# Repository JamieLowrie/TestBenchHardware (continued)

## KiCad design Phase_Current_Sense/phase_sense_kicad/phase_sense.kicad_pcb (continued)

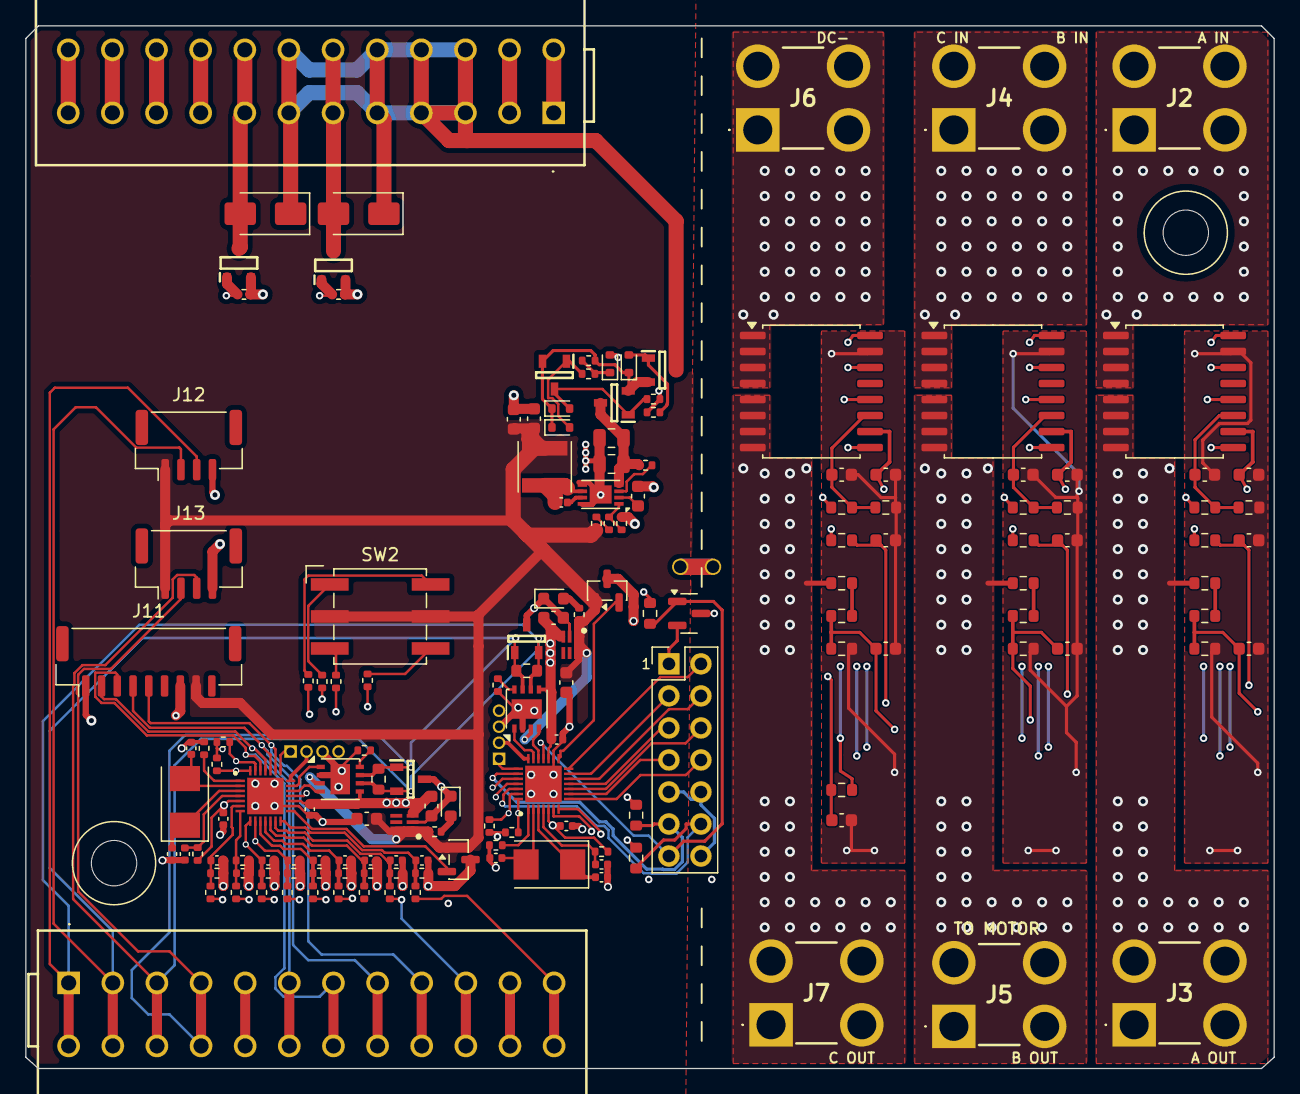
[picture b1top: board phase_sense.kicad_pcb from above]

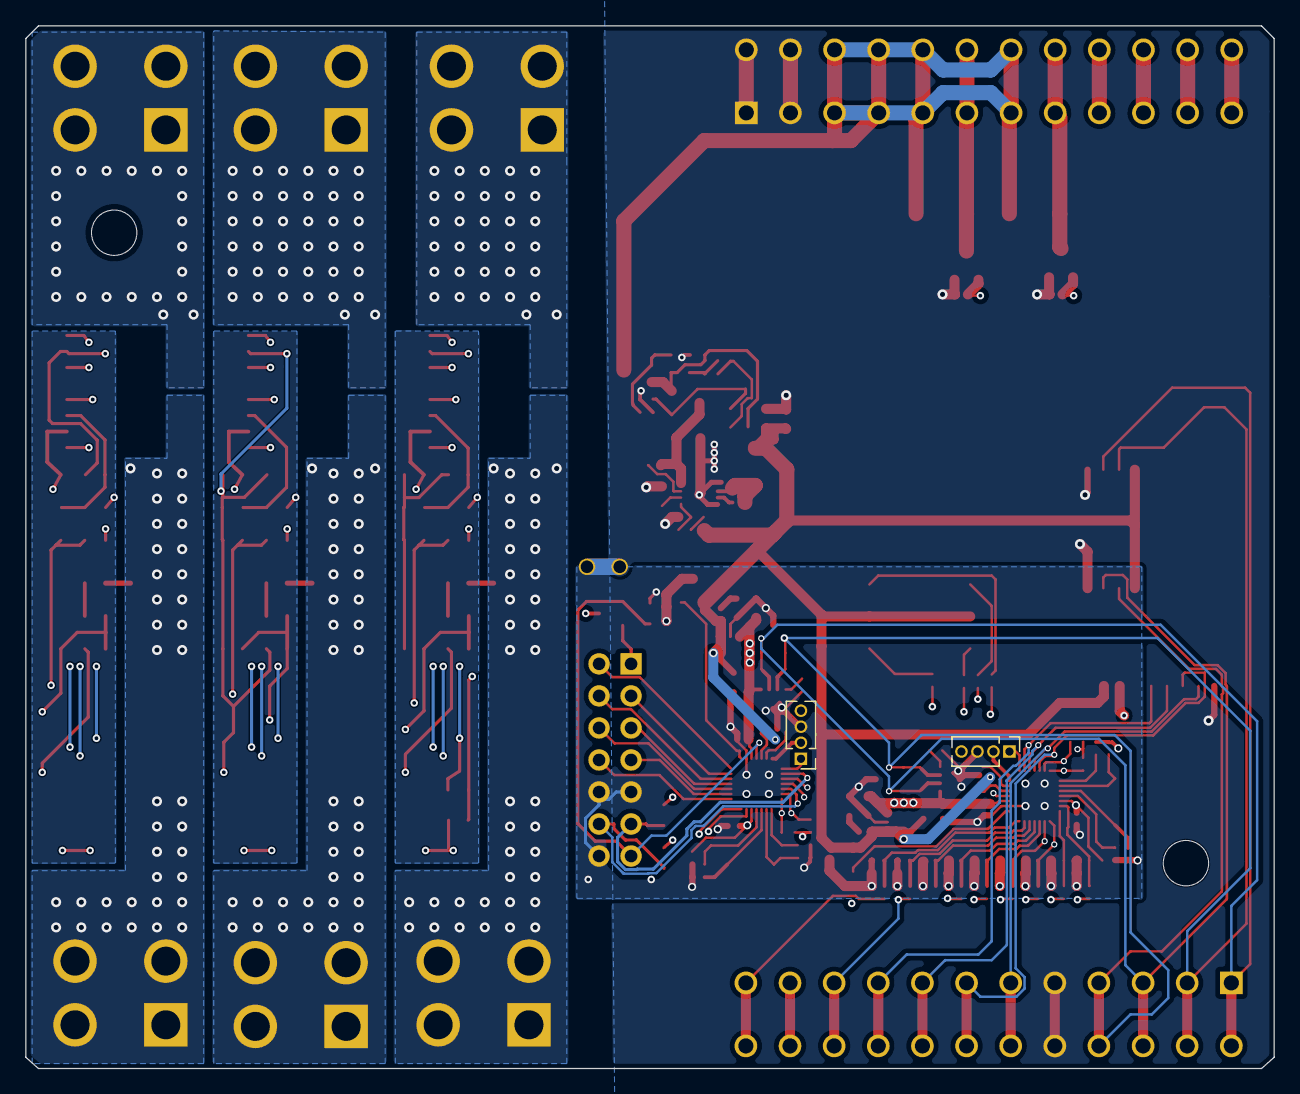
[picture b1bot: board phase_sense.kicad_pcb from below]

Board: 4 copper layers, 99.0 x 82.7 mm, 159 parts (2 on the bottom side), 101 nets.

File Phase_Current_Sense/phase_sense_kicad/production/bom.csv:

Designator,Footprint,Quantity,Value,LCSC Part #
C1,0603,1,10u,C19702
"C10, C18, C4, C6, C7",0603,5,22uF,C59461
"C11, C12, C21, C22, C31, C32",0603,6,100n,C14663
"C13, C23, C33",0603,3,10n,C57112
"C14, C24, C34",0603,3,22n,C21122
"C15, C19, C29, C35, C40, C42, C5",0402,7,0.1uF,C1525
"C16, C17, C8, C9",0402,4,20pF,C1554
"C2, C3",0805,2,10uF,C15850
"C20, C25, C26, C27, C38, C39",0402,6,1nF,C1523
"C28, C36, C37",0402,3,10nF,C15195
"C30, C41",0603,2,4.7uF, C19666
"D1, D3, D4",D_SOD-523,3,Zener 15V,C550633
"D11, D12",D_SMA,2,SS310,C15874
D2,D_SOD-523,1,Zener 25V,C559071
"D5, D6",0603,2,LED,C2286
"H1, H2",CDIB_Pillar_No6_Screw,2,No6,
"IC1, IC3",SON50P150X150X80-6N,2,TLV70033DSER,C97256
"IC2, IC4",QFN40P400X400X80-29N-D,2,CH32V203G6U6,C5142280
"IC6, IC7",SOTFL95P240X110-3N,2,ZXMS6004FFQ-7,C95063
J1,PinHeader_2x07_P2.54mm_Vertical,1,TO_MCU,
"J10, J9",PinHeader_1x04_P1.27mm_Vertical,2,1.27Debug,C161692
J11,JST_GH_BM09B-GHS-TBT_1x09-1MP_P1.25mm_Vertical,1,Conn_01x08_Pin,DNF
"J12, J13",JST_GH_BM04B-GHS-TBT_1x04-1MP_P1.25mm_Vertical,2,CAN,DNF
"J2, J3, J4, J5, J6, J7",AMT0440007DB0000G,6,AMT0440007DB0000G,C481447
"J20, J25",26011112,2,2601-1112,
L1,L_Vishay_IFSC-1515AH_4x4x1.8mm,1,22uH,C5363803
Q1,SOT-23,1,AO3401A,C15127
"Q2, Q4",SOT95P230X110-3N,2,60V2APMOS,C5148659
Q3,SOT95P230X110-3N,1,60VPMOS,C5148659
"R1, R12, R2, R22, R3, R32, R4",0603,7,10k,C25804
"R10, R40, R41, R42, R43, R5, R53, R6, R60, R63, R64, R65, R66, R7, R8, R9",0402,16,10K,C25744
"R102, R103",0402,2,22K,C25768
"R11, R21, R31",0603,3,33k,C4216
"R13, R23, R33",0603,3,1k,C21190
"R14, R15, R24, R25, R34, R35",0603,6,47k,C25819
"R16, R26, R36",0603,3,2.7k,C13167
R17,0402,1,51K,C25794
R18,0402,1,3.9K,C51721
"R19, R20, R27, R28, R29, R30, R37, R38, R39",0402,9,470K,C25790
"R44, R45, R46, R47, R48, R49, R50, R56, R57",0402,9,510K,C11616
"R51, R58",0402,2,1K,C11702
"R52, R59",0603,2,DNF,DNF
"R54, R55, R61, R62",0402,4,2K,C4109
SW2,Nidec_Copal_SH-7010B,1,SW_Coded_SH-7050,C5183894
"U1, U2, U3",SOIC-16W_7.5x10.3mm_P1.27mm,3,ACS37002LMABTR-066B3,C3684355
U4,DFN-8-1EP_3x2mm_P0.5mm_EP1.75x1.45mm,1,MCP16311MNY,C510882
"U5, U7",DFN-8-1EP_3x3mm_P0.65mm_EP1.55x2.4mm,2,TJA1044GTK/3Z,C2157795
"U6, U8",SOT-23,2,REF3025,C11334
"Y1, Y2",Crystal_SMD_5032-2Pin_5.0x3.2mm,2,8Mhz, C115962
"Z1, Z2",SOT95P230X110-3N,2,"PESD1CAN,215",C15771

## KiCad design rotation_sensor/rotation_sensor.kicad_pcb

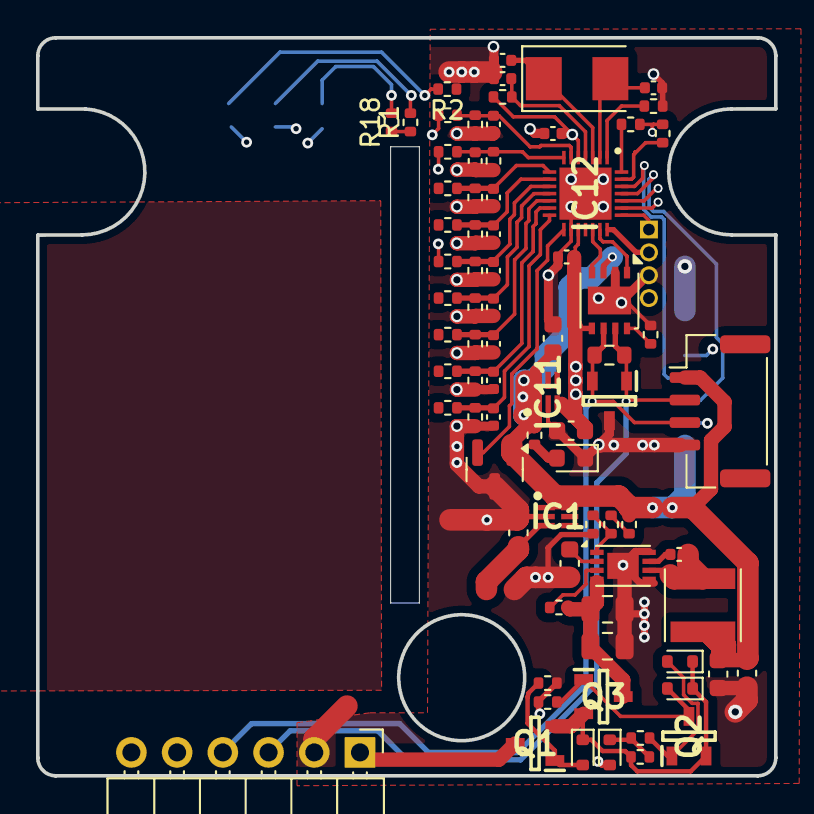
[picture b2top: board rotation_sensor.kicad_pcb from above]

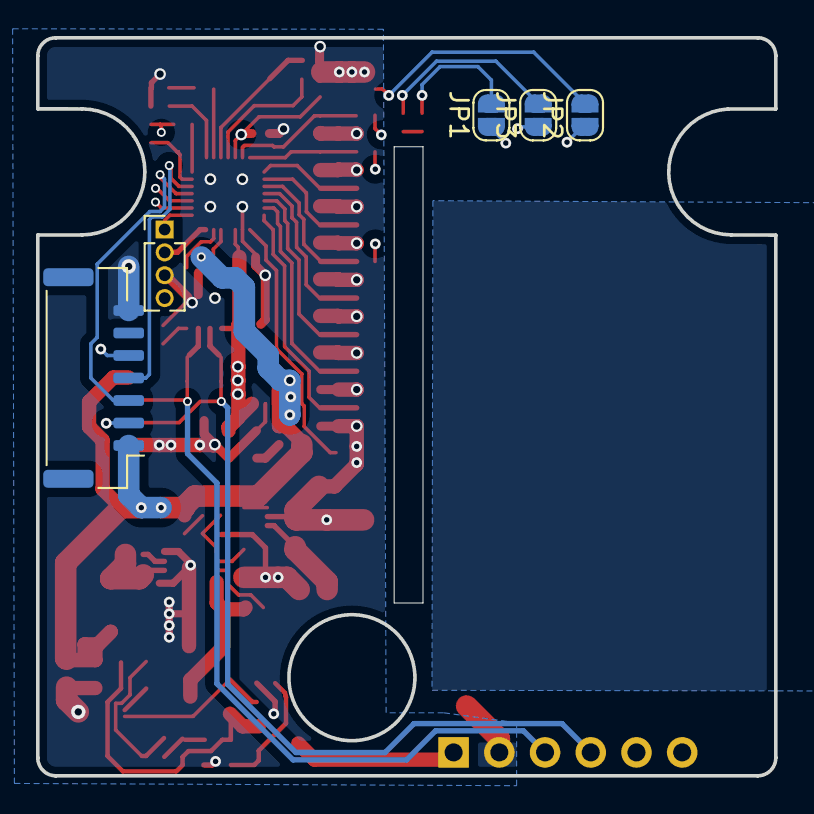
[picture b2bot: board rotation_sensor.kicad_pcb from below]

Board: 4 copper layers, 41.0 x 41.0 mm, 83 parts (5 on the bottom side), 51 nets.

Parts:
C17, C18: 10uF; C_0805_2012Metric
C19, C21, C22, C23, C202: 22uF; C_0603_1608Metric
C20, C203, C213, C215: 0.1uF; C_0402_1005Metric
C200, C201: 20pF; C_0402_1005Metric
C204, C205, C206, C207, C211, C212: 1nF; C_0402_1005Metric
C208, C209, C210: 10nF; C_0402_1005Metric
C214: 4.7uF; C_0603_1608Metric
D1, D3, D4: Zener 15V; D_SOD-523
D2: Zener 25V; D_SOD-523
D8: LED; LED_0603_1608Metric
IC1, IC11: TLV70033DSER; SON50P150X150X80-6N
IC12: CH32V203G6U6; QFN40P400X400X80-29N-D
J2: CAN; JST_GH_BM04B-GHS-TBT_1x04-1MP_P1.25mm_Vertical
J5: SPI; JST_GH_BM07B-GHS-TBT_1x07-1MP_P1.25mm_Vertical
J7: Conn_01x06_Pin; PinHeader_1x06_P2.54mm_Horizontal
J32: 1.27Debug; PinHeader_1x04_P1.27mm_Vertical
JP1, JP2, JP3: ID; SolderJumper-2_P1.3mm_Open_RoundedPad1.0x1.5mm
L1: 22uH; L_Vishay_IFSC-1515AH_4x4x1.8mm
Q1, Q3: 60V2APMOS; SOT95P230X110-3N
Q2: 60VPMOS; SOT95P230X110-3N
R1, R2, R10, R11, R14, R15, R16, R17, R18, R192, R193, R205: 10K; R_0402_1005Metric
R12: 51K; R_0402_1005Metric
R13: 3.9K; R_0402_1005Metric
R183, R184, R185, R186, R187, R188, R189, R190, R191: 470K; R_0402_1005Metric
R194, R195, R196, R197, R198, R199, R200, R201, R202: 510K; R_0402_1005Metric
R203: 1K; R_0402_1005Metric
R204: DNF; R_0603_1608Metric
R206, R207: 2K; R_0402_1005Metric
U6: MCP16311MNY; DFN-8-1EP_3x2mm_P0.5mm_EP1.75x1.45mm
U24: TJA1044GTK/3Z; DFN-8-1EP_3x3mm_P0.65mm_EP1.55x2.4mm
U25: REF3025; SOT-23
Y7: 8Mhz; Crystal_SMD_5032-2Pin_5.0x3.2mm
Z5: PESD1CAN,215; SOT95P230X110-3N

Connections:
+3V3: C23.2, IC1.3 (OUT)
+5V: C21.1, C22.1, C214.1, IC1.1 (IN), IC1.6 (EN), IC11.1 (IN), IC11.6 (EN), J2.1, J5.1, L1.2, R1.1, R2.1, R13.2, R18.1, R203.1, U24.3 (VCC), U25.1 (IN)
+12V: C17.1, C18.1, Q3.3 (D), R10.1, U6.4 (Vin)
/CAN_H: J2.2, J7.3, R204.1, U24.7 (CANH), Z5.1
/CAN_L: J2.3, J7.4, R204.2, U24.6 (CANL), Z5.2
/Micro/3V3: C202.2, C213.2, C215.2, IC11.3 (OUT), IC12.5 (VDDA), IC12.17 (VDD), J32.4, R192.1, R206.1, R207.1, U24.5 (VIO)
/Micro/ADC0: C204.2, IC12.6 (PA0/WKUP/ADC0), R183.2, R194.1
/Micro/ADC1: C205.2, IC12.7 (PA1/ADC1), R184.2, R195.1
/Micro/ADC2_UART_TXB: C206.2, IC12.8 (PA2/ADC2), R185.2, R196.1
/Micro/ADC3_UART_RXA: C207.2, IC12.9 (PA3/ADC3), R186.2, R197.1
/Micro/ADC4: C208.2, IC12.10 (PA4/ADC4), R187.2, R198.1
/Micro/ADC5: C209.2, IC12.11 (PA5/ADC5), R188.2, R199.1
/Micro/ADC6: C210.2, IC12.12 (PA6/ADC6), R189.2, R200.1
/Micro/ADC7: C211.2, IC12.13 (PA7/ADC7), R190.2, R201.1
/Micro/ADC8: C212.2, IC12.14 (PB0/ADC8), R191.2, R202.1
/Micro/ADC9: IC12.15 (PB1/ADC9), U25.2 (OUT)
/Micro/AINA 0-5V: JP1.1 (A), R183.1
/Micro/AINB 0-5V: JP2.1 (A), R184.1
/Micro/AINE 0-5V: JP3.1 (A), R187.1
/Micro/BOOT0: IC12.1 (BOOT0/PB8), R205.2
/Micro/CAN_RX: IC12.19 (PA10/PA11/USB1DM), U24.4 (RXD)
/Micro/CAN_TX: IC12.20 (PA12/USB1DP), U24.1 (TXD)
/Micro/NRST: C203.2, IC12.4 (NRST), R192.2
/Micro/OSC_IN: C200.2, IC12.2 (OSC_IN/PD0), Y7.2
/Micro/OSC_OUT: C201.2, IC12.3 (OSC_OUT/PD1), Y7.1
/Micro/SWCLK: IC12.22 (PA14/SWCLK), J32.1
/Micro/SWDIO: IC12.21 (PA13/SWDIO), J32.2
/POWER: J7.1, Q1.3 (D)
/SCL: IC12.27 (PB6), R207.2
/SDA: IC12.28 (PB7), R206.2
/SPI_CLK: IC12.24 (PB3), J5.2
/SPI_MISO: IC12.25 (PB4), J5.3
/SPI_MOSI: IC12.26 (PB5), J5.4
/SPI_NSS: IC12.23 (PA15), J5.5
GND: C17.2, C18.2, C19.2, C21.2, C22.2, C23.1, C200.1, C201.1, C202.1, C203.1, C204.1, C205.1, C206.1, C207.1, C208.1, C209.1, C210.1, C211.1, C212.1, C213.1, C214.2, C215.1, D2.2 (A), D8.1 (K), IC1.2 (GND), IC11.2 (GND), IC12.16 (VSS), IC12.29 (GND), J2.4, J5.7, J7.2, J32.3, R11.2, R14.1, R17.1, R193.2, R194.2, R195.2, R196.2, R197.2, R198.2, R199.2, R200.2, R201.2, R202.2, R205.1, U6.5 (PGND), U6.8 (AGND), U6.9 (PAD), U24.2 (GND), U24.9 (GND), U25.3 (GND), Z5.3
unnamed: D1.2 (A), Q1.1 (G), R14.2
unnamed: D1.1 (K), D3.1 (K), D4.1 (K), Q1.2 (S), Q2.2 (S), Q3.2 (S), R15.2
unnamed: D2.1 (K), R15.1, R16.1
unnamed: D3.2 (A), Q2.1 (G), R16.2
unnamed: D4.2 (A), Q2.3 (D), Q3.1 (G), R17.2
unnamed: D8.2 (A), R203.2
unnamed: JP1.2 (B), R18.2
unnamed: JP2.2 (B), R2.2
unnamed: JP3.2 (B), R1.2
unnamed: R12.2, R13.1
unnamed: C20.1, U6.7 (BOOST)
unnamed: R10.2, U6.3 (EN)
unnamed: C20.2, L1.1, U6.6 (SW)
unnamed: C19.1, U6.2 (Vcc)
unnamed: R11.1, R12.1, U6.1 (Vfb)
unnamed: R193.1, U24.8 (S)

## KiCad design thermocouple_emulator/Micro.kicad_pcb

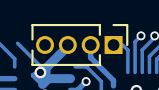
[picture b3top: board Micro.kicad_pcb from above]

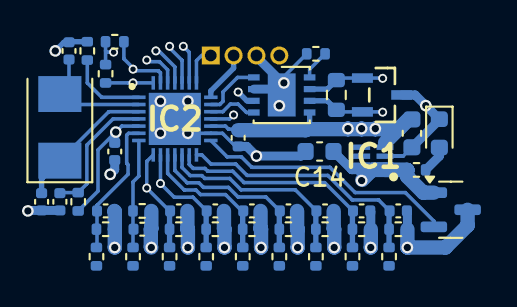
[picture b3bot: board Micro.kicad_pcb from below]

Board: 4 copper layers, 49 parts (48 on the bottom side), 27 nets.

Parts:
C1, C2: 20pF; C_0402_1005Metric
C3: 22uF; C_0603_1608Metric
C4, C15, C16: 0.1uF; C_0402_1005Metric
C5, C6, C7, C8, C12, C13: 1nF; C_0402_1005Metric
C9, C10, C11: 10nF; C_0402_1005Metric
C14: 4.7uF; C_0603_1608Metric
D1: LED; LED_0603_1608Metric
IC1: TLV70033DSER; SON50P150X150X80-6N
IC2: CH32V203G6U6; QFN40P400X400X80-29N-D
J1: 1.27Debug; PinHeader_1x04_P1.27mm_Vertical
R1, R2, R3, R4, R5, R6, R7, R8, R9: 470K; R_0402_1005Metric
R11, R12, R25: 10K; R_0402_1005Metric
R13, R14, R15, R16, R17, R18, R19, R20, R21: 510K; R_0402_1005Metric
R23: 1K; R_0402_1005Metric
R24: DNF; R_0603_1608Metric
R26, R27: DNF/2K; R_0402_1005Metric
U1: TJA1044GTK/3Z; DFN-8-1EP_3x3mm_P0.65mm_EP1.55x2.4mm
U2: REF3025; SOT-23
Y1: 8Mhz; Crystal_SMD_5032-2Pin_5.0x3.2mm
Z1: PESD1CAN,215; SOT95P230X110-3N

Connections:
/3V3: C3.2, C15.2, C16.2, IC1.3 (OUT), IC2.5 (VDDA), IC2.17 (VDD), J1.4, R11.1, R26.1, R27.1, U1.5 (VIO)
/5V: C14.1, IC1.1 (IN), IC1.6 (EN), R23.1, U1.3 (VCC), U2.1 (IN)
/ADC0: C5.2, IC2.6 (PA0/WKUP/ADC0), R1.2, R13.1
/ADC1: C6.2, IC2.7 (PA1/ADC1), R2.2, R14.1
/ADC2_UART_TXB: C7.2, IC2.8 (PA2/ADC2), R3.2, R15.1
/ADC3_UART_RXA: C8.2, IC2.9 (PA3/ADC3), R4.2, R16.1
/ADC4: C9.2, IC2.10 (PA4/ADC4), R5.2, R17.1
/ADC5: C10.2, IC2.11 (PA5/ADC5), R6.2, R18.1
/ADC6: C11.2, IC2.12 (PA6/ADC6), R7.2, R19.1
/ADC7: C12.2, IC2.13 (PA7/ADC7), R8.2, R20.1
/ADC8: C13.2, IC2.14 (PB0/ADC8), R9.2, R21.1
/ADC9: IC2.15 (PB1/ADC9), U2.2 (OUT)
/BOOT0: IC2.1 (BOOT0/PB8), R25.2
/CAN_H: R24.1, U1.7 (CANH), Z1.1
/CAN_L: R24.2, U1.6 (CANL), Z1.2
/CAN_RX: IC2.19 (PA10/PA11/USB1DM), U1.4 (RXD)
/CAN_TX: IC2.20 (PA12/USB1DP), U1.1 (TXD)
/NRST: C4.2, IC2.4 (NRST), R11.2
/OSC_IN: C1.2, IC2.2 (OSC_IN/PD0), Y1.2
/OSC_OUT: C2.2, IC2.3 (OSC_OUT/PD1), Y1.1
/SWCLK: IC2.22 (PA14/SWCLK), J1.1
/SWDIO: IC2.21 (PA13/SWDIO), J1.2
/UART_RX_SDA: IC2.28 (PB7), R26.2
/UART_TX_SCL: IC2.27 (PB6), R27.2
GNDA: C1.1, C2.1, C3.1, C4.1, C5.1, C6.1, C7.1, C8.1, C9.1, C10.1, C11.1, C12.1, C13.1, C14.2, C15.1, C16.1, D1.1 (K), IC1.2 (GND), IC2.16 (VSS), IC2.29 (GND), J1.3, R12.2, R13.2, R14.2, R15.2, R16.2, R17.2, R18.2, R19.2, R20.2, R21.2, R25.1, U1.2 (GND), U1.9 (GND), U2.3 (GND), Z1.3
unnamed: D1.2 (A), R23.2
unnamed: R12.1, U1.8 (S)

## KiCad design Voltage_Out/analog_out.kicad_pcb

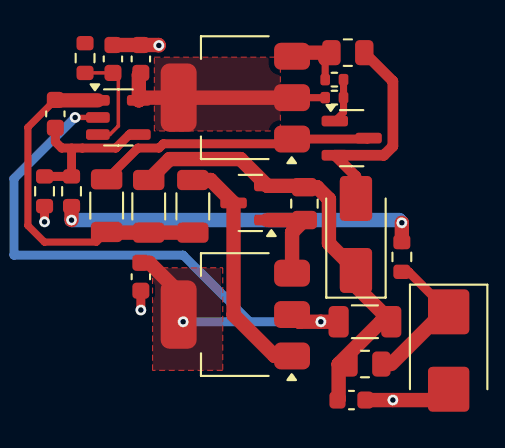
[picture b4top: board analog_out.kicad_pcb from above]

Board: 2 copper layers, 25 parts (0 on the bottom side), 15 nets.

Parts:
C1, C2: 100n 50V; C_0603_1608Metric
C3: 3n3 X7R; C_0603_1608Metric
C4: 47p C0G; C_0603_1608Metric
C5: 1n 50V; C_0603_1608Metric
D1: SS110; D_SMA
D2: SMBJ33A; D_SMB
Q1: MMBT3904; SOT-23
Q2: SS8550; SOT-23
Q3: BCP56-16; SOT-223-3_TabPin2
Q4: BCP53-16; SOT-223-3_TabPin2
R1: 2k; R_0603_1608Metric
R2: 1k; R_0603_1608Metric
R3: 40k2 0.1%; R_0603_1608Metric
R4: 10k 0.1%; R_0603_1608Metric
R5: 1k; R_1206_3216Metric
R6, R7, R12: 10k 1206; R_1206_3216Metric
R8: 47K; R_0402_1005Metric
R9: 1k; R_0402_1005Metric
R10: 4R7; R_0805_2012Metric
R11: 47R; R_0805_2012Metric
R13: 4R7 0805; R_0805_2012Metric
U1: OPA197IDBVR; SOT-23-5

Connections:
+16V: C1.1, Q3.2 (C), R8.1, U1.5 (V+)
-5V: C2.1, Q4.2 (C), R12.2, U1.2 (V-)
/AOUT: R2.2, R3.1
/AOUT_B: D2.1 (K), R2.1, R13.2
/LIMB_B: Q1.1 (B), R8.2, R9.1
/OUT_INT_B: C5.1, D1.1 (K), Q2.2 (E), R6.2, R11.1, R12.1, R13.1
GND: C1.2, C2.2, C3.2, C5.2, D2.2 (A), R4.1
unnamed: C4.2, R5.1, R6.1, R7.1, U1.1
unnamed: D1.2 (A), Q1.2 (E), R10.2
unnamed: Q1.3 (C), Q3.1 (B), R5.2
unnamed: Q2.1 (B), Q4.3 (E), R11.2
unnamed: Q2.3 (C), Q4.1 (B), R7.2
unnamed: Q3.3 (E), R9.2, R10.1
unnamed: C3.1, R1.2, U1.3 (+)
unnamed: C4.1, R3.2, R4.2, U1.4 (-)

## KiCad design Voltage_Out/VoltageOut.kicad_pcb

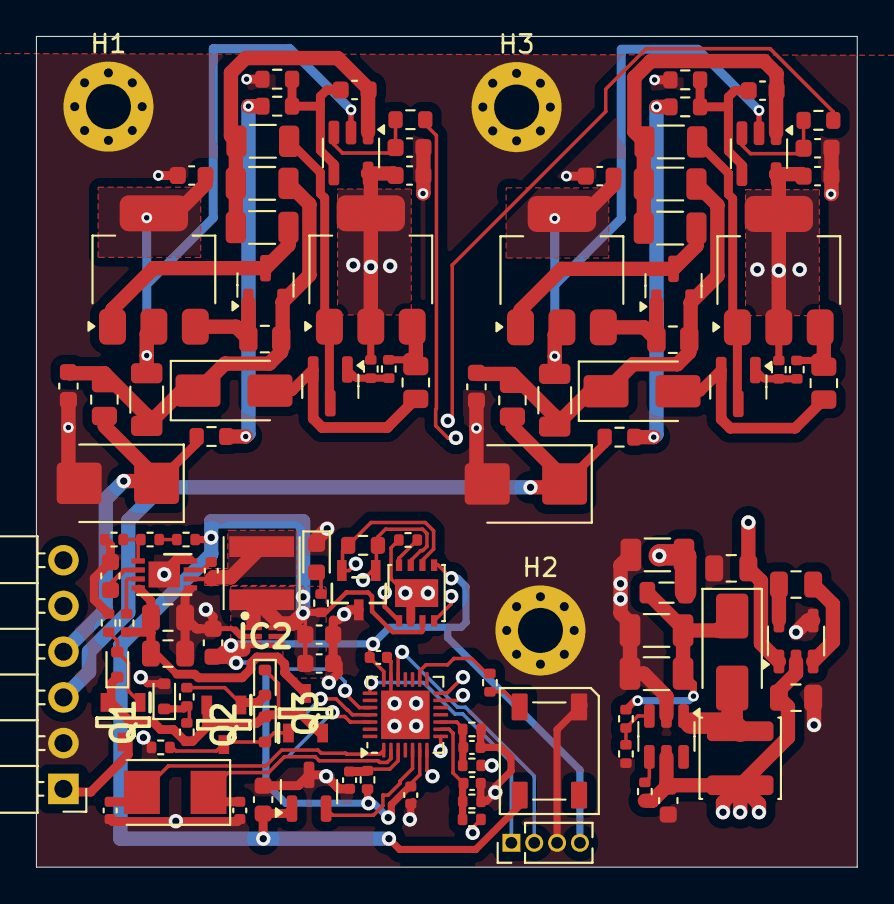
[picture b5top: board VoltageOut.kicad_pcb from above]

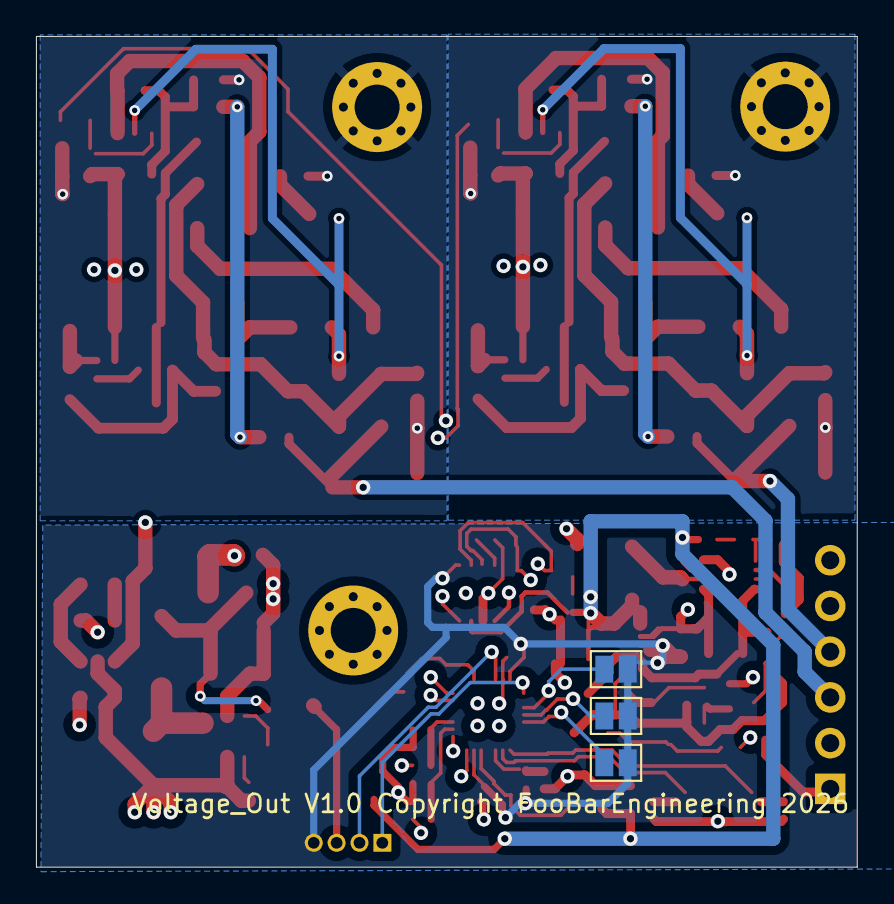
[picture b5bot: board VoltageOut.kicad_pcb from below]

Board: 4 copper layers, 45.6 x 46.2 mm, 122 parts (3 on the bottom side), 69 nets.

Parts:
C1, C4: 10uF; C_0805_2012Metric
C2, C5: 20pF; C_0402_1005Metric
C3: 4.7uF; C_0603_1608Metric
C6, C11, C13, C14: 22uF; C_0603_1608Metric
C7, C10, C12, C15: 0.1uF; C_0402_1005Metric
C8, C9: 1nF; C_0402_1005Metric
C16, C17, C28, C29: 100n 50V; C_0603_1608Metric
C18, C30: 3n3 X7R; C_0603_1608Metric
C19, C31: 47p C0G; C_0603_1608Metric
C20, C32: 1n 50V; C_0603_1608Metric
C21: 22u; C_0603_1608Metric
C22, C23, C24: 10u 50V; C_1206_3216Metric
C25, C26, C27: 1u; C_0805_2012Metric
D1, D3, D4: Zener 15V; D_SOD-523
D2: Zener 25V; D_SOD-523
D5: LED; LED_0603_1608Metric
D6: WS2812B; LED_WS2812B_PLCC4_5.0x5.0mm_P3.2mm
D7, D10: SS110; D_SMA
D8, D11: SMBJ33A; D_SMB
D9: SS34; D_SMA
FB1: 100R@100M; L_0805_2012Metric
H1, H2, H3: MountingHole_Pad; MountingHole_2.5mm_Pad_Via
IC1: CH32V305GBU6; QFN-28-1EP_4x4mm_P0.4mm_EP2.7x2.7mm
IC2: TLV70033DSER; SON50P150X150X80-6N
J1: Conn_01x06_Pin; PinHeader_1x06_P2.54mm_Horizontal
J2: 1.27Debug; PinHeader_1x04_P1.27mm_Vertical
JP1, JP2, JP3: Jumper_2_Open; SolderJumper-2_P1.3mm_Open_Pad1.0x1.5mm
L1: 22uH; L_Vishay_IFSC-1515AH_4x4x1.8mm
L2: 4.7uH 3.2A; L_Changjiang_FNR4030S
Q1, Q3: 60V2APMOS; SOT95P230X110-3N
Q2: 60VPMOS; SOT95P230X110-3N
Q4, Q8: MMBT3904; SOT-23
Q5, Q9: SS8550; SOT-23
Q6, Q10: BCP56-16; SOT-223-3_TabPin2
Q7, Q11: BCP53-16; SOT-223-3_TabPin2
R1, R2, R3, R4, R5, R8, R9, R12: 10K; R_0402_1005Metric
R6, R7: 470K; R_0402_1005Metric
R10, R11, R13: 51K; R_0402_1005Metric
R14: 3.9K; R_0402_1005Metric
R15: DNF; R_0603_1608Metric
R16: 1K; R_0402_1005Metric
R17: 22; R_0402_1005Metric
R18, R34: 2k; R_0603_1608Metric
R19, R35: 1k; R_0603_1608Metric
R20, R36: 40k2 0.1%; R_0603_1608Metric
R21, R37: 10k 0.1%; R_0603_1608Metric
R22, R38: 1k; R_1206_3216Metric
R23, R24, R29, R39, R40, R45: 10k 1206; R_1206_3216Metric
R25, R41: 47K; R_0402_1005Metric
R26, R42: 1k; R_0402_1005Metric
R27, R43: 4R7; R_0805_2012Metric
R28, R44: 47R; R_0805_2012Metric
R30, R46: 4R7 0805; R_0805_2012Metric
R31: 100k; R_0402_1005Metric
R32: 255k 1%; R_0402_1005Metric
R33: 10k 1%; R_0402_1005Metric
U1: REF3025; SOT-23
U2: MCP16311MNY; DFN-8-1EP_3x2mm_P0.5mm_EP1.75x1.45mm
U3: TJA1044GTK/3Z; DFN-8-1EP_3x3mm_P0.65mm_EP1.55x2.4mm
U4, U7: OPA197IDBVR; SOT-23-5
U5: MT3608; SOT-23-6
U6: TPS60403DBVR; SOT-23-5
Y1: 8Mhz; Crystal_SMD_5032-2Pin_5.0x3.2mm
Z1: PESD1CAN,215; SOT95P230X110-3N

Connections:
+3V3: C12.2, C14.2, C15.2, IC1.6 (VIO), IC1.21 (VDD), IC2.3 (OUT), J2.4, JP1.1 (A), JP2.1 (A), JP3.1 (A), R8.1, U3.5 (VIO)
+5V: C3.1, C11.1, C13.1, C21.1, C25.1, D6.1 (VDD), IC2.1 (IN), IC2.6 (EN), L1.2, L2.1, R14.2, R16.1, R31.1, U1.1 (IN), U3.3 (VCC), U5.5 (IN), U6.2 (IN)
+12V: C1.1, C4.1, Q3.3 (D), R5.1, U2.4 (Vin)
+16V: C16.1, C24.1, C28.1, FB1.2, Q6.2 (C), Q10.2 (C), R25.1, R41.1, U4.5 (V+), U7.5 (V+)
-5V: C17.1, C27.1, C29.1, Q7.2 (C), Q11.2 (C), R29.2, R45.2, U4.2 (V-), U6.1 (OUT), U7.2 (V-)
/DAC1: IC1.7 (PA4/SPI1NSS/SPI3NSS1/PA1), R18.1
/DAC2: IC1.8 (PA5/SPI1SCK), R34.1
/FB_1: R6.1, R19.2, R20.1
/FB_2: R7.1, R35.2, R36.1
/MicroProcessor/ADC6: C8.2, IC1.9 (PA6/SPI1MISO), R6.2, R10.1
/MicroProcessor/ADC7: C9.2, IC1.10 (PA7/SPI1MOSI), R7.2, R11.1
/MicroProcessor/ADC13: IC1.5 (PC3/UART7RX), U1.2 (OUT)
/MicroProcessor/CAN_H: J1.5, R15.1, U3.7 (CANH), Z1.1
/MicroProcessor/CAN_L: J1.6, R15.2, U3.6 (CANL), Z1.2
/MicroProcessor/CAN_RX: IC1.13 (PB12/SPI2NSS/CAN2RX), U3.4 (RXD)
/MicroProcessor/CAN_TX: IC1.14 (PB13/SPI2SCK/UART3CTS/CAN2TX), U3.1 (TXD)
/MicroProcessor/ID1: IC1.26 (PD2/UART5RX/SD_CMD), JP1.2 (B)
/MicroProcessor/ID2: IC1.25 (PC12/UART5TX/SPI3MOSI1/SD_CK), JP2.2 (B)
/MicroProcessor/ID3: IC1.24 (PC11/UART4RX/SPI3MISO1/SD_D3), JP3.2 (B)
/MicroProcessor/NRST: C7.2, IC1.3 (NRST), R8.2
/MicroProcessor/OSC_IN: C2.2, IC1.1 (OSC_IN/PD0), Y1.2
/MicroProcessor/OSC_OUT: C5.2, IC1.2 (OSC_OUT/PD1), Y1.1
/MicroProcessor/SWCLK: IC1.22 (PA14/SWCLK/UART3RX2), J2.1
/MicroProcessor/SWDIO: IC1.19 (PA13/SWDIO/UART3TX2), J2.2
/analog_out1/AOUT_B: D11.1 (K), J1.4, R35.1, R46.2
/analog_out1/LIMB_B: Q8.1 (B), R41.2, R42.1
/analog_out1/OUT_INT_B: C32.1, D10.1 (K), Q9.2 (E), R39.2, R44.1, R45.1, R46.1
/analog_out/AOUT_B: D8.1 (K), J1.3, R19.1, R30.2
/analog_out/LIMB_B: Q4.1 (B), R25.2, R26.1
/analog_out/OUT_INT_B: C20.1, D7.1 (K), Q5.2 (E), R23.2, R28.1, R29.1, R30.1
GND: C1.2, C2.1, C3.2, C4.2, C5.1, C6.2, C7.1, C8.1, C9.1, C11.2, C12.1, C13.2, C14.1, C15.1, C16.2, C17.2, C18.2, C20.2, C21.2, C22.2, C23.2, C24.2, C25.2, C27.2, C28.2, C29.2, C30.2, C32.2, D2.2 (A), D5.1 (K), D6.3 (VSS), D8.2 (A), D11.2 (A), H1.1, H2.1, H3.1, IC1.20 (VSS/GND), IC1.29 (GND), IC2.2 (GND), J1.2, J2.3, R1.1, R4.1, R9.2, R10.2, R11.2, R12.2, R21.1, R33.2, R37.1, U1.3 (GND), U2.5 (PGND), U2.8 (AGND), U2.9 (PAD), U3.2 (GND), U3.9 (GND), U5.2 (GND), U6.4 (GND), Z1.3
unnamed: C19.2, R22.1, R23.1, R24.1, U4.1
unnamed: C31.2, R38.1, R39.1, R40.1, U7.1
unnamed: D1.2 (A), Q1.1 (G), R1.2
unnamed: D1.1 (K), D3.1 (K), D4.1 (K), Q1.2 (S), Q2.2 (S), Q3.2 (S), R2.2
unnamed: D2.1 (K), R2.1, R3.1
unnamed: D3.2 (A), Q2.1 (G), R3.2
unnamed: D4.2 (A), Q2.3 (D), Q3.1 (G), R4.2
unnamed: D5.2 (A), R16.2
unnamed: D6.4 (DIN), R17.1
unnamed: D7.2 (A), Q4.2 (E), R27.2
unnamed: D9.2 (A), L2.2, U5.1 (SW)
unnamed: C22.1, C23.1, D9.1 (K), FB1.1, R32.1
unnamed: D10.2 (A), Q8.2 (E), R43.2
unnamed: IC1.16 (PB15/SPI2MOSI/UART1TX2), R17.2
unnamed: J1.1, Q1.3 (D)
unnamed: Q4.3 (C), Q6.1 (B), R22.2
unnamed: Q5.1 (B), Q7.3 (E), R28.2
unnamed: Q5.3 (C), Q7.1 (B), R24.2
unnamed: Q6.3 (E), R26.2, R27.1
unnamed: Q8.3 (C), Q10.1 (B), R38.2
unnamed: Q10.3 (E), R42.2, R43.1
unnamed: Q9.3 (C), Q11.1 (B), R40.2
unnamed: Q9.1 (B), Q11.3 (E), R44.2
unnamed: R13.2, R14.1
unnamed: C10.1, U2.7 (BOOST)
unnamed: R5.2, U2.3 (EN)
unnamed: C10.2, L1.1, U2.6 (SW)
unnamed: C6.1, U2.2 (Vcc)
unnamed: R12.1, R13.1, U2.1 (Vfb)
unnamed: R9.1, U3.8 (S)
unnamed: C18.1, R18.2, U4.3 (+)
unnamed: C19.1, R20.2, R21.2, U4.4 (-)
unnamed: R31.2, U5.4 (EN)
unnamed: R32.2, R33.1, U5.3 (FB)
unnamed: C26.1, U6.5 (CFLY+)
unnamed: C26.2, U6.3 (CFLY-)
unnamed: C30.1, R34.2, U7.3 (+)
unnamed: C31.1, R36.2, R37.2, U7.4 (-)

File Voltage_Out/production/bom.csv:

Designator,Footprint,Quantity,Value,LCSC Part #
"C1, C4",0805,2,10uF,C15850
"C10, C12, C15, C7",0402,4,0.1uF,C1525
"C11, C13, C14, C6",0603,4,22uF,C59461
"C16, C17, C28, C29",0603,4,100n 50V,C14663
"C18, C30",0603,2,3n3 X7R,C1613
"C19, C31",0603,2,47p C0G,C1671
"C2, C5",0402,2,20pF,C1554
"C20, C32",0603,2,1n 50V,C1588
C21,0603,1,22u,C59461
"C22, C23, C24",1206,3,10u 50V,C13585
"C25, C26, C27",0805,3,1u,C28323
C3,0603,1,4.7uF, C19666
"C8, C9",0402,2,1nF,C1523
"D1, D3, D4",D_SOD-523,3,Zener 15V,C550633
"D10, D7",D_SMA,2,SS110,C2482
"D11, D8",D_SMB,2,SMBJ33A,C353366
D2,D_SOD-523,1,Zener 25V,C559071
D5,0603,1,LED,C2286
D6,LED_WS2812B_PLCC4_5.0x5.0mm_P3.2mm,1,WS2812B,C2874885
D9,D_SMA,1,SS34,C8678
FB1,0805,1,100R@100M,C1015
IC1,QFN-28-1EP_4x4mm_P0.4mm_EP2.7x2.7mm,1,CH32V305GBU6,C19100608
IC2,SON50P150X150X80-6N,1,TLV70033DSER,C97256
J1,PinHeader_1x06_P2.54mm_Horizontal,1,Conn_01x06_Pin,C492414
L1,L_Vishay_IFSC-1515AH_4x4x1.8mm,1,22uH,C5363803
L2,L_Changjiang_FNR4030S,1,4.7uH 3.2A,C167874
"Q1, Q3",SOT95P230X110-3N,2,60V2APMOS,C5148659
"Q10, Q6",SOT-223-3_TabPin2,2,BCP56-16,C2909805
"Q11, Q7",SOT-223-3_TabPin2,2,BCP53-16,C148109
Q2,SOT95P230X110-3N,1,60VPMOS,C5148659
"Q4, Q8",SOT-23,2,MMBT3904,C20526
"Q5, Q9",SOT-23,2,SS8550,C8542
"R1, R12, R2, R3, R4, R5, R8, R9",0402,8,10K,C25744
"R10, R11, R13",0402,3,51K,C25794
R14,0402,1,3.9K,C51721
"R16, R26, R42",0402,3,1K,C11702
R17,0402,1,22,C25092
"R18, R34",0603,2,2k,C22975
"R19, R35",0603,2,1k,C21190
"R20, R36",0603,2,40k2 0.1%,C2989618
"R21, R37",0603,2,10k 0.1%,C95204
"R22, R38",1206,2,1k,C4410
"R23, R24, R29, R39, R40, R45",1206,6,10k 1206,C17902
"R25, R41",0402,2,47K,C25792
"R27, R43",0805,2,4R7,C17675
"R28, R44",0805,2,47R,C17714
"R30, R46",0805,2,4R7 0805,C17675
R31,0402,1,100k,C25741
R32,0402,1,255k 1%,C25857
R33,0402,1,10k 1%,C25744
"R6, R7",0402,2,470K,C25790
U1,SOT-23,1,REF3025,C11334
U2,DFN-8-1EP_3x2mm_P0.5mm_EP1.75x1.45mm,1,MCP16311MNY,C510882
U3,DFN-8-1EP_3x3mm_P0.65mm_EP1.55x2.4mm,1,TJA1044GTK/3Z,C2157795
"U4, U7",SOT-23-5,2,OPA197IDBVR,C221351
U5,SOT-23-6,1,MT3608,C84817
U6,SOT-23-5,1,TPS60403DBVR,C11338
Y1,Crystal_SMD_5032-2Pin_5.0x3.2mm,1,8Mhz, C115962
Z1,SOT95P230X110-3N,1,"PESD1CAN,215",C15771

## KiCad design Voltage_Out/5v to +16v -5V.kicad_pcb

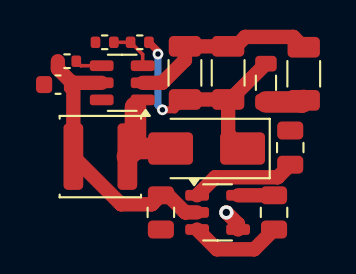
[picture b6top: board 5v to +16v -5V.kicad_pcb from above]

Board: 4 copper layers, 15 parts (0 on the bottom side), 10 nets.

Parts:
C1: 22u; C_0603_1608Metric
C2, C3, C4: 10u 50V; C_1206_3216Metric
C5, C6, C7: 1u; C_0805_2012Metric
D5: SS34; D_SMA
FB1: 100R@100M; L_0805_2012Metric
L2: 4.7uH 3.2A; L_Changjiang_FNR4030S
R3: 100k; R_0402_1005Metric
R4: 255k 1%; R_0402_1005Metric
R5: 10k 1%; R_0402_1005Metric
U1: MT3608; SOT-23-6
U2: TPS60403DBVR; SOT-23-5

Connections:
/5V: C1.1, C5.1, L2.1, R3.1, U1.5 (IN), U2.2 (IN)
/-5V: C7.1, U2.1 (OUT)
/-16V: C4.1, FB1.2
GND: C1.2, C2.2, C3.2, C4.2, C5.2, C7.2, R5.2, U1.2 (GND), U2.4 (GND)
unnamed: D5.2 (A), L2.2, U1.1 (SW)
unnamed: C2.1, C3.1, D5.1 (K), FB1.1, R4.1
unnamed: R3.2, U1.4 (EN)
unnamed: R4.2, R5.1, U1.3 (FB)
unnamed: C6.1, U2.5 (CFLY+)
unnamed: C6.2, U2.3 (CFLY-)

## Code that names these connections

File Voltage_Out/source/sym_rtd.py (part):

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   [("8", "VCC2", "power_in"), ("7", "CANH", "bidirectional"), ("6", "CANL", "bidirectional"), ("5", "GND2", "power_in")])
ic("PESD1CAN", [("1", "K1", "passive"), ("2", "K2", "passive")], [("3", "A", "passive")], width=10.16, ref="D")
ic("CH32V203G6U6",
   [("17", "VDD", "power_in"), ("5", "VDDA", "power_in"), ("4", "NRST", "input"), ("1", "BOOT0/PB8", "input"),
    ("2", "PD0/OSC_IN", "input"), ("3", "PD1/OSC_OUT", "output"), ("6", "PA0", "bidirectional"), ("7", "PA1", "bidirectional"),
    ("10", "PA4", "bidirectional"), ("8", "PA2", "bidirectional"), ("9", "PA3", "bidirectional"),
    ("16", "VSS", "power_in"), ("29", "EP", "power_in")],
   [("11", "PA5", "bidirectional"), ("12", "PA6", "bidirectional"), ("13", "PA7", "bidirectional"), ("14", "PB0", "bidirectional"),
    ("15", "PB1", "bidirectional"), ("18", "PA9", "bidirectional"), ("19", "PA10/PA11", "bidirectional"), ("20", "PA12", "bidirectional"),
    ("21", "PA13/SWDIO", "bidirectional"), ("22", "PA14/SWCLK", "bidirectional"), ("23", "PA15", "bidirectional"),
    ("24", "PB3", "bidirectional"), ("25", "PB4", "bidirectional"), ("26", "PB5", "bidirectional"),
    ("27", "PB6", "bidirectional"), ("28", "PB7", "bidirectional")], width=25.4)
ic("DAC8812",
   [("13", "VDD", "power_in"), ("11", "~{CS}", "input"), ("16", "CLK", "input"), ("9", "SDI", "input"),
    ("15", "~{LDAC}", "input"), ("10", "~{RS}", "input"), ("14", "MSB", "input"), ("12", "DGND", "power_in"),
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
